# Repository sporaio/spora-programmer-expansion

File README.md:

# Spora Programmer Expansion

This is the repository of the Spora Programmer Expansion. Spora is coin-sized open source programmable board, equipped with multiple sensors, a powerful MCU and Bluetooth module to transmit your collected data.

With this board you can expand Spora's functioanlity into anything you want. Find out more about Spora at https://sporaio.com/

Spora's main board code is in this repository: https://github.com/sporaio/spora-board

## Contributors

This project is open source, under the BSD licence. You can contribute to it and be part of this great community.

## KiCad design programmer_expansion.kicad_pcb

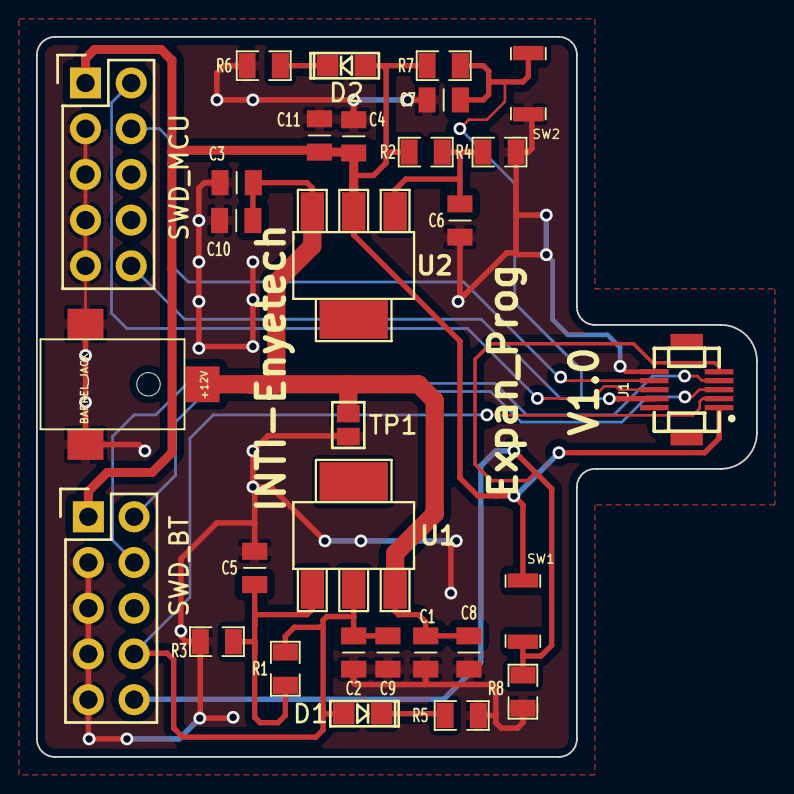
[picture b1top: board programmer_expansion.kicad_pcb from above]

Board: 2 copper layers, 40.0 x 40.0 mm, 30 parts (0 on the bottom side), 14 nets.

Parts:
+12V: BARREL_JACK; Pj-38-smt
C1, C2, C3, C4, C5, C6: 10uF; c_0805
C7, C8, C9, C10, C11: 0.1uF; c_0805
D1, D2: Led; LED-0805
J1: DF12B-3.0-10DS-0.5V-81; df12(3.0)-10ds-0.5v
R1: 270; r_0805
R2: 470; r_0805
R3: 1,2k; r_0805
R4: 280; r_0805
R5: 10K; r_0805
R6, R7: 4,7K; r_0805
R8: 4K7; r_0805
SW1, SW2: SIDE_SW; B3U_1000PB
SWD_BT: SWD_BT; Pin_Header_Straight_2x05
SWD_MCU: SWD_MCU; Pin_Header_Straight_2x05
TP1: TP1; GS2
U1, U2: LM1117; sot223

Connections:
+3V3: C4.1, C11.1, D2.2, J1.1, R2.1, R7.2, SW1.2, SWD_BT.1, SWD_MCU.1, U2.2
+12V: +12V.1, C1.1, C3.1, C8.1, C10.1, TP1.1, U1.3, U2.3
/RST_BT: J1.5, R8.2, SW1.1, SWD_BT.10
/SWD_CLK_BT: J1.4, SWD_BT.4
/SWD_CLK_MCU: J1.7, SWD_MCU.4
/SWD_DIO_BT: J1.3, SWD_BT.2
/SWD_DIO_MCU: J1.8, SWD_MCU.2
/~RESET_b: C7.1, J1.9, R7.1, SW2.2, SWD_MCU.10
GND: +12V.2, +12V.3, C1.2, C2.2, C3.2, C4.2, C5.2, C6.2, C7.2, C8.2, C9.2, C10.2, C11.2, J1.6, R3.2, R4.2, R5.1, R6.1, R8.1, SW2.1, SWD_BT.3, SWD_BT.5, SWD_BT.7, SWD_BT.9, SWD_MCU.3, SWD_MCU.5, SWD_MCU.7, SWD_MCU.9, TP1.2
unnamed: C5.1, R1.2, R3.1, U1.1
unnamed: C6.1, R2.2, R4.1, U2.1
unnamed: D1.1, R5.2
unnamed: D2.1, R6.2
VPP: C2.1, C9.1, D1.2, J1.2, R1.1, SWD_BT.8, U1.2

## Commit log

2018-10-05 Expansionn Board initial commit
    It includes all files to build your own Spora's expansion board.

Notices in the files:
programmer_expansion.kicad_pcb:
BSD License. See LICENSE.txt
